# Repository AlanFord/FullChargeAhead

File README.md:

# FullChargeAhead
Full Charge Ahead pcb for the Contextual Electronics course

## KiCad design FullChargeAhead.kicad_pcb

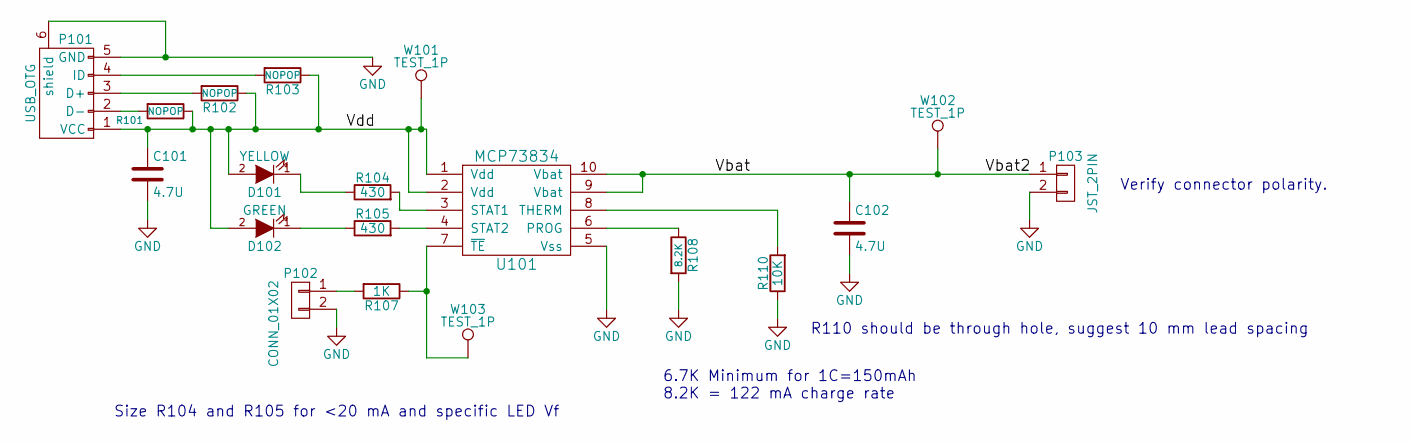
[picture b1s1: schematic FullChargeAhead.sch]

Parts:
C101, C102: 4.7U; C_0805_HandSoldering
D101: YELLOW; LED_0805; MPN LTST-C171KSKT
D102: GREEN; LED_0805; MPN LTST-C171GKT
P101: USB_OTG; 10118193; MPN 10118193-0001LF
P102: CONN_01X02; Pin_Header_Straight_1x02
P103: JST_2PIN; JST_Type_PH_Side_Entry_1x02_Pitch2.00mm; MPN S2B-PH-K-S(LF)(SN)
R101, R102, R103: NOPOP; R_0805_HandSoldering
R104, R105: 430; R_0805_HandSoldering
R107: 1K; R_0805_HandSoldering
R108: 8.2K; R_0805_HandSoldering
R110: 10K; Resistor_Horizontal_RM10mm
U101: MCP73834; MSOP-10_3x3mm_Pitch0.5mm; MPN MCP73834-FCI/UN
W101, W102, W103: TEST_1P; Measurement_Point_Round-SMD-Pad_Small

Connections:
/Vbat: C102.1, P103.1, U101.9 (Vbat), U101.10 (Vbat), W102.1
/Vdd: C101.1, D101.2 (A), D102.2 (A), P101.1 (VCC), R101.1, R102.1, R103.1, U101.1 (Vdd), U101.2 (Vdd), W101.1
GND: C101.2, C102.2, P101.5 (GND), P101.6 (shield), P102.2, P103.2, R108.2, R110.1, U101.5 (Vss)
unnamed: D101.1 (K), R104.1
unnamed: D102.1 (K), R105.1
unnamed: P101.2 (D-), R101.2
unnamed: P101.3 (D+), R102.2
unnamed: P101.4 (ID), R103.2
unnamed: P102.1, R107.2
unnamed: R104.2, U101.3 (STAT1)
unnamed: R105.2, U101.4 (STAT2)
unnamed: R107.1, U101.7 (~TE), W103.1
unnamed: R108.1, U101.6 (PROG)
unnamed: R110.2, U101.8 (THERM)

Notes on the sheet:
Size R104 and R105 for <20 mA and specific LED Vf
R110 should be through hole, suggest 10 mm lead spacing
Verify connector polarity.
6.7K Minimum for 1C=150mAh 8.2K = 122 mA charge rate

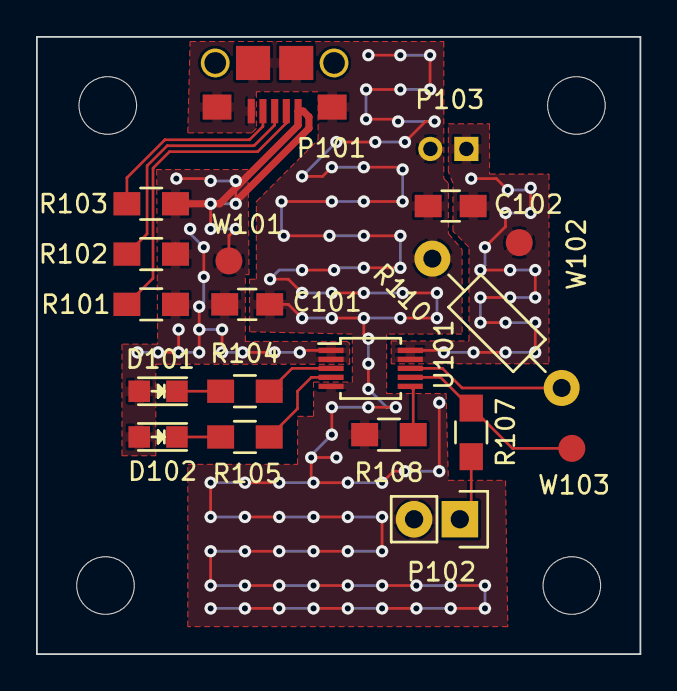
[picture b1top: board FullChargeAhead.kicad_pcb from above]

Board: 2 copper layers, 33.5 x 34.3 mm, 19 parts (0 on the bottom side), 14 nets.

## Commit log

2016-09-15 initial commit of schematic and pcb layout
2016-09-21 starting rev 2
2016-09-21 added Vbat connectors for current monitoring
2016-09-21 added MPN for screw terminals
2016-10-17 initial board layout and copper fills
2016-10-31 new usb connector, via stiching, and gerbers
2016-11-15 generated gerbers including solder stencil
